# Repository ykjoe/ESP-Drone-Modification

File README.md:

# ESP-Drone

<br>

<br>

For a full tutorial check out our [ESP32 Drone Article](https://circuitdigest.com/microcontroller-projects/DIY-wifi-controlled-drone).
For working video:  [How to build an ESP32 Drone](https://youtu.be/uzZjk0TQKtU).

Drones have rapidly evolved from niche hobbies to versatile tools with a wide range of applications, from photography to agriculture or even for defense and military purposes. Depending on the application, features and payload capacity their price will vary from pocket changes to a few million. Even though the basic principle behind these drones may appear simple, there is a lot of technology and computation that goes behind it for proper operations and a desired result from these drones. For example, maintaining stability while in the air requires precision sensors such as a Gyroscope and proper processing of reading taken with it. In this project we are going to make such a drone which can be easily controlled using our phones.
This DIY drone is small in size and can be built using easily available components such as ESP32 modules, MPU6050 IMU, coreless motors and plastic propellers.

<br>**For anyone who is trying to flash the firmware using ESP32 Flash Download Tool, here are the file offsets for each binary**
<br>**0x1000 bootloader.bin**
<br>**0x8000 partition-table.bin**
<br>**0x10000 ESPDrone.bin**
<br>
[Note: As this projects are very simple we are only providing the code, schemaitic, and a few essential images if you want to get the images or code explanations do check out the Circuit Digest website.
<br>
<br>

Copy from: https://github.com/Circuit-Digest/ESP-Drone.git

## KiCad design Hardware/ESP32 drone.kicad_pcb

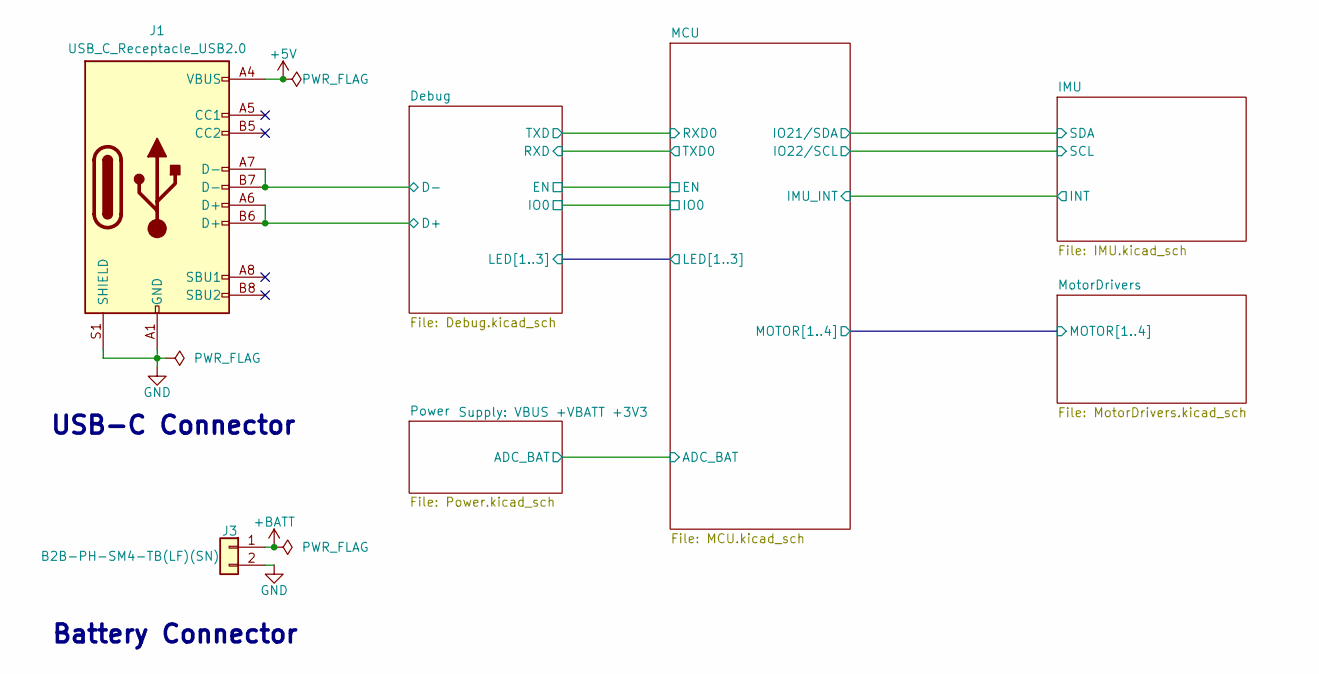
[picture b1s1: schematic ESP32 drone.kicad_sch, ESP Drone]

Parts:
J1: USB_C_Receptacle_USB2.0; USB_C_Receptacle_HRO_TYPE-C-31-M-12
J3: B2B-PH-SM4-TB(LF)(SN); JST_PH_B2B-PH-SM4-TB_1x02-1MP_P2.00mm_Vertical

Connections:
+5V: J1.A4 (VBUS), J1.A9 (VBUS), J1.B4 (VBUS), J1.B9 (VBUS); also elsewhere on the board
+BATT: J3.1; also elsewhere on the board
/Debug/D+: J1.A6 (D+), J1.B6 (D+); also elsewhere on the board
/Debug/D-: J1.A7 (D-), J1.B7 (D-); also elsewhere on the board
GND: J1.A1 (GND), J1.A12 (GND), J1.B1 (GND), J1.B12 (GND), J1.S1 (SHIELD), J3.2; also elsewhere on the board

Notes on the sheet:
Battery Connector
USB-C Connector

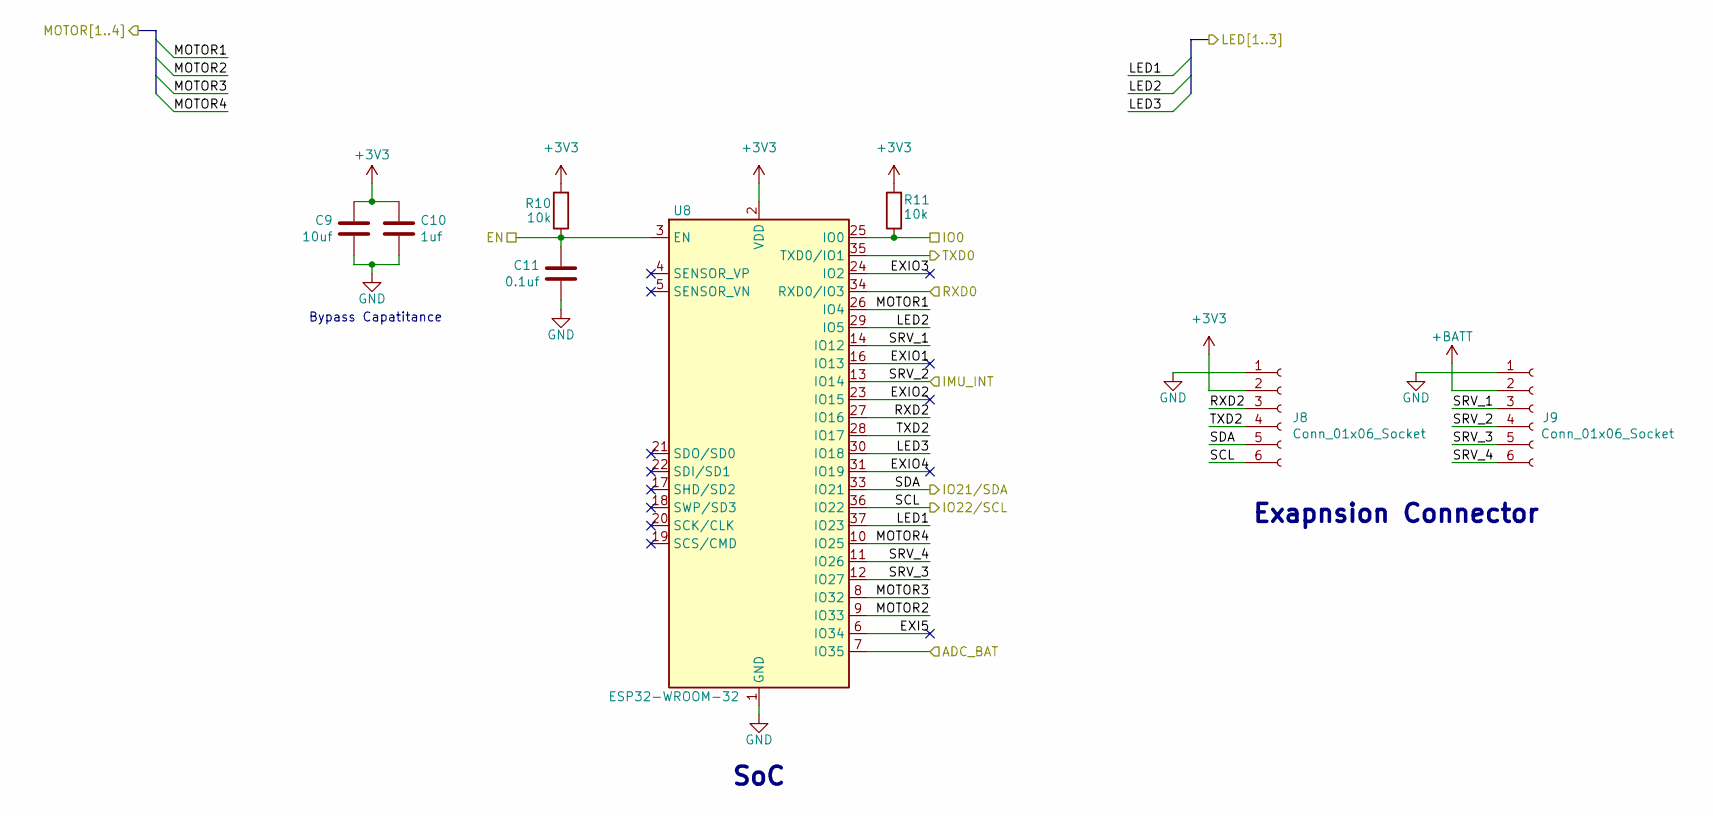
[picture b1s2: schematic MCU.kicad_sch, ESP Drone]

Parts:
C9: 10uf; C_0603_1608Metric
C10: 1uf; C_0603_1608Metric
C11: 0.1uf; C_0603_1608Metric
J8, J9: Conn_01x06_Socket; PinHeader_1x06_P2.54mm_Vertical
R10, R11: 10k; R_0603_1608Metric
U8: ESP32-WROOM-32

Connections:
+3V3: C9.1, C10.1, J8.2, R10.2, R11.2, U8.2 (VDD); also elsewhere on the board
+BATT: J9.2; also elsewhere on the board
/Debug/EN: C11.1, R10.1, U8.3 (EN); also elsewhere on the board
/Debug/IO0: R11.1, U8.25 (IO0); also elsewhere on the board
/Debug/LED1: U8.37 (IO23); also elsewhere on the board
/Debug/LED2: U8.29 (IO5); also elsewhere on the board
/Debug/LED3: U8.30 (IO18); also elsewhere on the board
/Debug/RXD: U8.35 (TXD0/IO1); also elsewhere on the board
/Debug/TXD: U8.34 (RXD0/IO3); also elsewhere on the board
/MCU/ADC_BAT: U8.7 (IO35); also elsewhere on the board
/MCU/EXI5: U8.6 (IO34)
/MCU/EXIO1: U8.16 (IO13)
/MCU/EXIO2: U8.23 (IO15)
/MCU/EXIO3: U8.24 (IO2)
/MCU/EXIO4: U8.31 (IO19)
/MCU/MOTOR1: U8.26 (IO4); also elsewhere on the board
/MCU/MOTOR2: U8.9 (IO33); also elsewhere on the board
/MCU/MOTOR3: U8.8 (IO32); also elsewhere on the board
/MCU/MOTOR4: U8.10 (IO25); also elsewhere on the board
/MCU/RXD2: J8.3, U8.27 (IO16)
/MCU/SCL: J8.6, U8.36 (IO22); also elsewhere on the board
/MCU/SDA: J8.5, U8.33 (IO21); also elsewhere on the board
/MCU/SRV_1: J9.3, U8.14 (IO12)
/MCU/SRV_2: J9.4, U8.13 (IO14); also elsewhere on the board
/MCU/SRV_3: J9.5, U8.12 (IO27)
/MCU/SRV_4: J9.6, U8.11 (IO26)
/MCU/TXD2: J8.4, U8.28 (IO17)
GND: C9.2, C10.2, C11.2, J8.1, J9.1, U8.1 (GND), U8.15 (GND), U8.38 (GND), U8.39 (GND); also elsewhere on the board

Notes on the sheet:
Exapnsion Connector
Bypass Capatitance
SoC

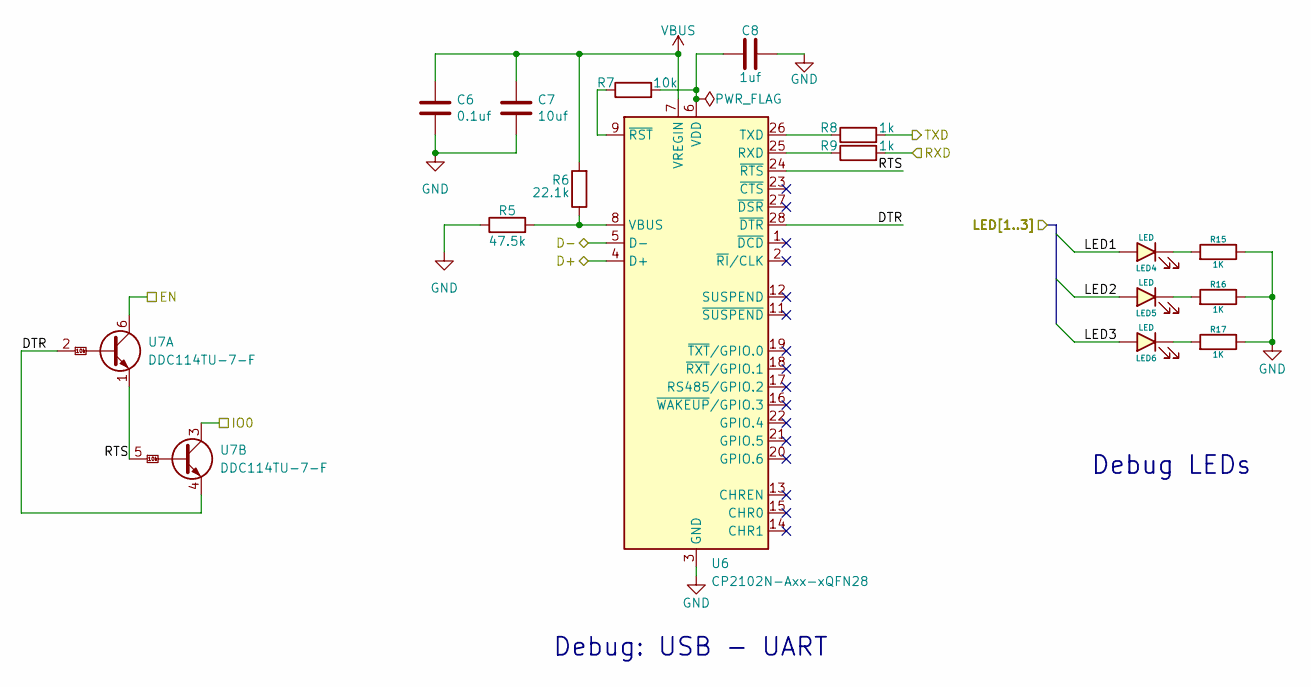
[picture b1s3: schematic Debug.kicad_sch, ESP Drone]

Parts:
C6: 0.1uf; C_0603_1608Metric
C7: 10uf; C_0603_1608Metric
C8: 1uf; C_0603_1608Metric
LED4, LED5, LED6: LED; LED_0603_1608Metric
R5: 47.5k; R_0603_1608Metric
R6: 22.1k; R_0603_1608Metric
R7: 10k; R_0603_1608Metric
R8, R9: 1k; R_0603_1608Metric
R15, R16, R17: 1K; R_0603_1608Metric
U6: CP2102N-Axx-xQFN28; QFN-28-1EP_5x5mm_P0.5mm_EP3.35x3.35mm
U7: DDC114TU-7-F; SOT-363_SC-70-6

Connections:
/Debug/D+: U6.4 (D+); also elsewhere on the board
/Debug/D-: U6.5 (D-); also elsewhere on the board
/Debug/DTR: U6.28 (~DTR), U7.2 (B1), U7.4 (E2)
/Debug/EN: U7.6 (C1); also elsewhere on the board
/Debug/IO0: U7.3 (C2); also elsewhere on the board
/Debug/LED1: LED4.2 (A); also elsewhere on the board
/Debug/LED2: LED5.2 (A); also elsewhere on the board
/Debug/LED3: LED6.2 (A); also elsewhere on the board
/Debug/RTS: U6.24 (~RTS), U7.1 (E1), U7.5 (B2)
/Debug/RXD: R9.2; also elsewhere on the board
/Debug/TXD: R8.2; also elsewhere on the board
GND: C6.2, C7.2, C8.2, R5.1, R15.1, R16.1, R17.1, U6.3 (GND), U6.29 (GND); also elsewhere on the board
unnamed: LED4.1 (K), R15.2
unnamed: LED5.1 (K), R16.2
unnamed: LED6.1 (K), R17.2
unnamed: R9.1, U6.25 (RXD)
unnamed: R8.1, U6.26 (TXD)
unnamed: R5.2, R6.1, U6.8 (VBUS)
unnamed: C8.1, R7.2, U6.6 (VDD)
unnamed: R7.1, U6.9 (~RST)
VBUS: C6.1, C7.1, R6.2, U6.7 (VREGIN); also elsewhere on the board

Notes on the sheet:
Debug LEDs
Debug: USB - UART

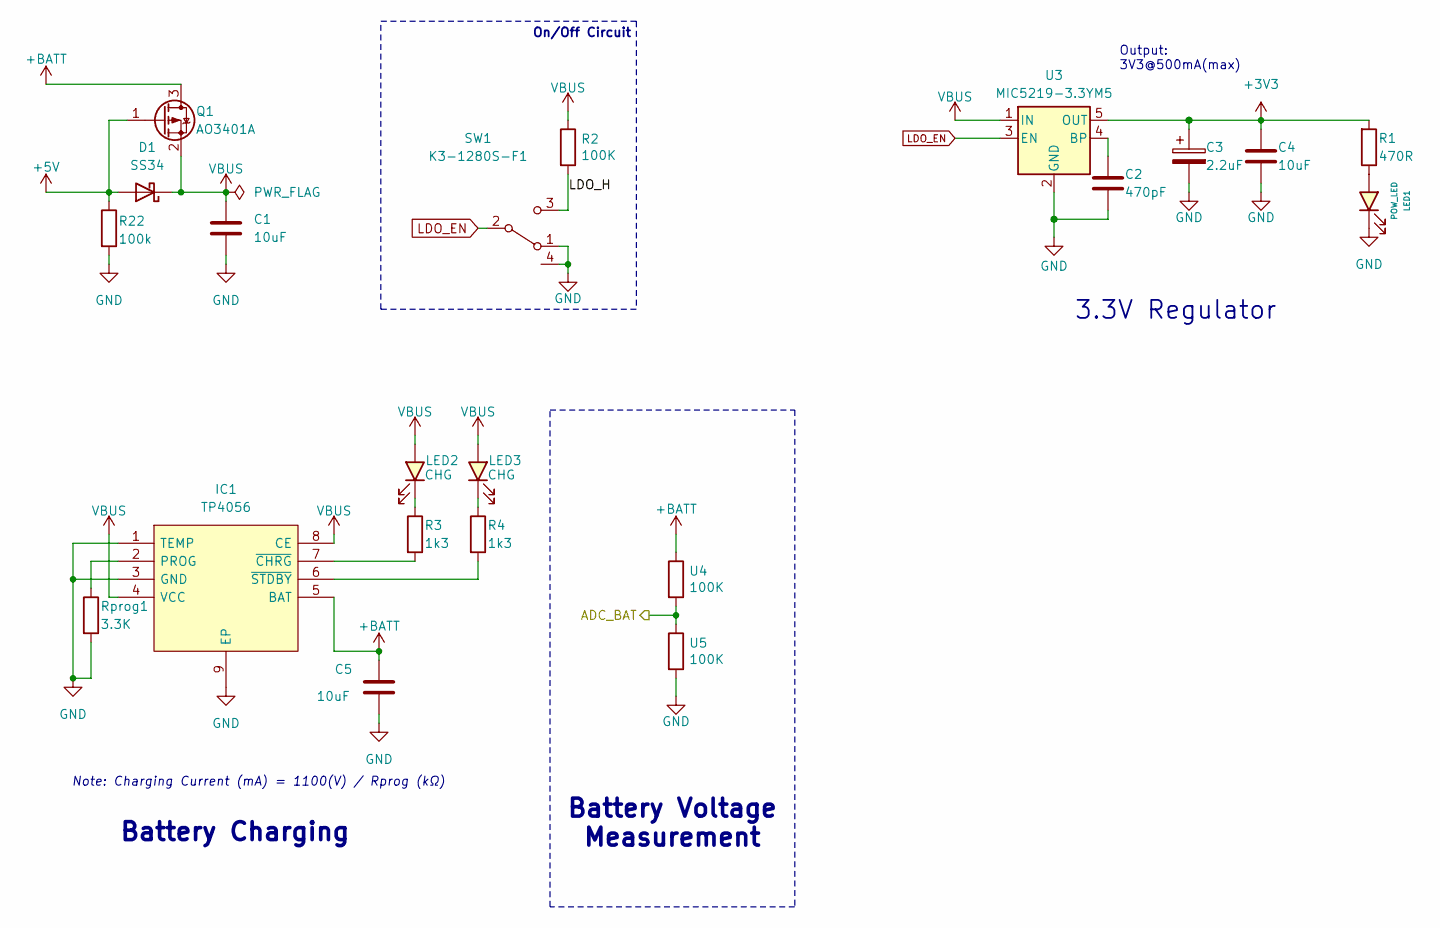
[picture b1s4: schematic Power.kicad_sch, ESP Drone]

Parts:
C1, C4, C5: 10uF; C_0603_1608Metric
C2: 470pF; C_0603_1608Metric
C3: 2.2uF; C_0805_2012Metric
D1: SS34; D_SMA
IC1: TP4056; SOIC127P600X175-9N; Manufacturer_Part_Number TP4056-42-ESOP8
LED1: POW_LED; LED_0603_1608Metric
LED2, LED3: CHG; LED_0603_1608Metric
Q1: AO3401A; SOT-23
R1: 470R; R_0603_1608Metric
R2: 100K; R_0603_1608Metric
R3, R4: 1k3; R_0603_1608Metric
R22: 100k; R_0603_1608Metric
Rprog1: 3.3K; R_0603_1608Metric
SW1: K3-1280S-F1; slide switch spdt
U3: MIC5219-3.3YM5; SOT-23-5
U4, U5: 100K; R_0603_1608Metric

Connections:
+3V3: C3.1, C4.1, R1.2, U3.5 (OUT); also elsewhere on the board
+5V: D1.2 (A), Q1.1 (G), R22.1; also elsewhere on the board
+BATT: C5.1, IC1.5 (BAT), Q1.3 (D), U4.1; also elsewhere on the board
/MCU/ADC_BAT: U4.2, U5.1; also elsewhere on the board
/Power/LDO_H: R2.2, SW1.3 (C)
GND: C1.2, C2.2, C3.2, C4.2, C5.2, IC1.1 (TEMP), IC1.3 (GND), IC1.9 (EP), LED1.1 (K), R22.2, Rprog1.2, SW1.1 (A), SW1.4, U3.2 (GND), U5.2; also elsewhere on the board
LDO_EN: SW1.2 (B), U3.3 (EN)
unnamed: IC1.2 (PROG), Rprog1.1
unnamed: IC1.7 (~CHRG), R3.2
unnamed: IC1.6 (~STDBY), R4.2
unnamed: LED1.2 (A), R1.1
unnamed: LED2.1 (K), R3.1
unnamed: LED3.1 (K), R4.1
unnamed: C2.1, U3.4 (BP)
VBUS: C1.1, D1.1 (K), IC1.4 (VCC), IC1.8 (CE), LED2.2 (A), LED3.2 (A), Q1.2 (S), R2.1, U3.1 (IN); also elsewhere on the board

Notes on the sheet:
Output: 3V3@500mA(max)
Note: Charging Current (mA) = 1100(V) / Rprog (kΩ)
Battery Voltage Measurement
Battery Charging
On/Off Circuit
3.3V Regulator

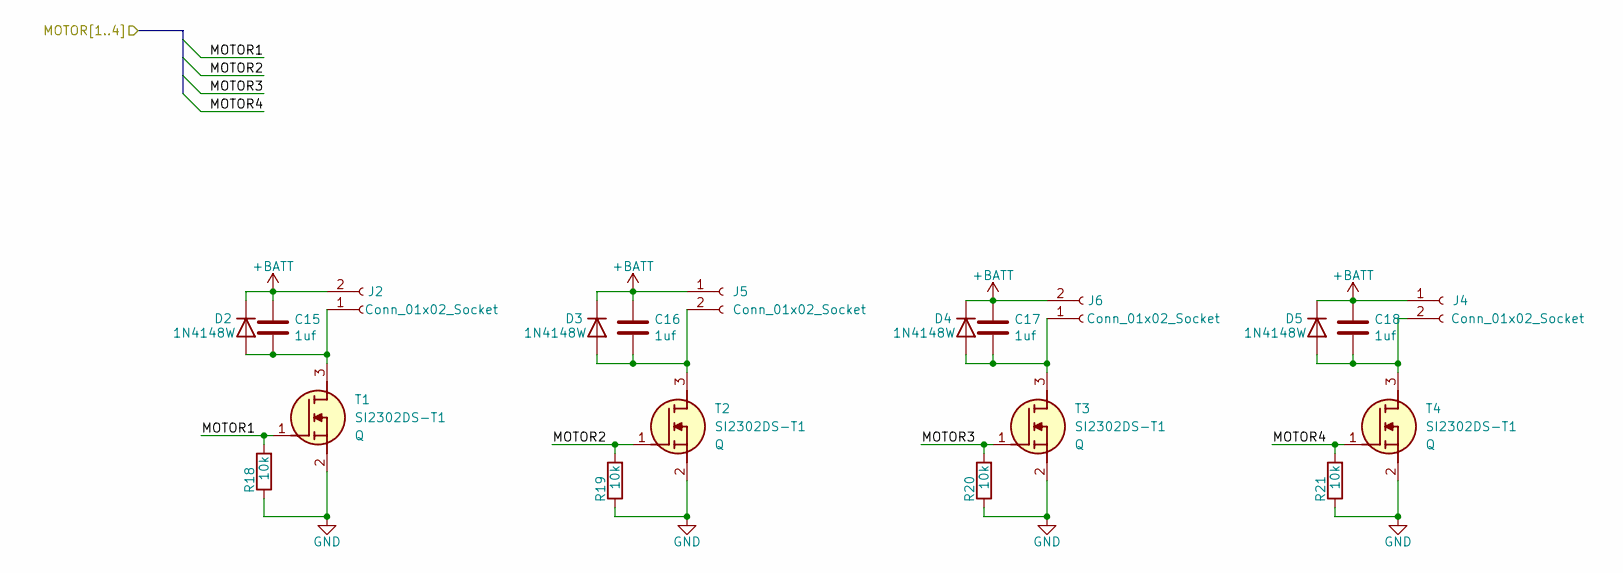
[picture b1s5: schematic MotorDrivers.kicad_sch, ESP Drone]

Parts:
C15, C16, C17, C18: 1uf; C_0603_1608Metric
D2, D3, D4, D5: 1N4148W; D_SOD-123
J2, J4, J5, J6: Conn_01x02_Socket; JST_GH_SM02B-GHS-TB_1x02-1MP_P1.25mm_Horizontal
R18, R19, R20, R21: 10k; R_0603_1608Metric
T1, T2, T3, T4: SI2302DS-T1; SOT95P237X112-3N; Mouser Part Number 781-SI2302DS

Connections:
+BATT: C15.1, C16.1, C17.1, C18.1, D2.1 (K), D3.1 (K), D4.1 (K), D5.1 (K), J2.2, J4.1, J5.1, J6.2; also elsewhere on the board
/MCU/MOTOR1: R18.2, T1.1 (G); also elsewhere on the board
/MCU/MOTOR2: R19.2, T2.1 (G); also elsewhere on the board
/MCU/MOTOR3: R20.2, T3.1 (G); also elsewhere on the board
/MCU/MOTOR4: R21.2, T4.1 (G); also elsewhere on the board
GND: R18.1, R19.1, R20.1, R21.1, T1.2 (S), T2.2 (S), T3.2 (S), T4.2 (S); also elsewhere on the board
unnamed: C15.2, D2.2 (A), J2.1, T1.3 (D)
unnamed: C16.2, D3.2 (A), J5.2, T2.3 (D)
unnamed: C17.2, D4.2 (A), J6.1, T3.3 (D)
unnamed: C18.2, D5.2 (A), J4.2, T4.3 (D)

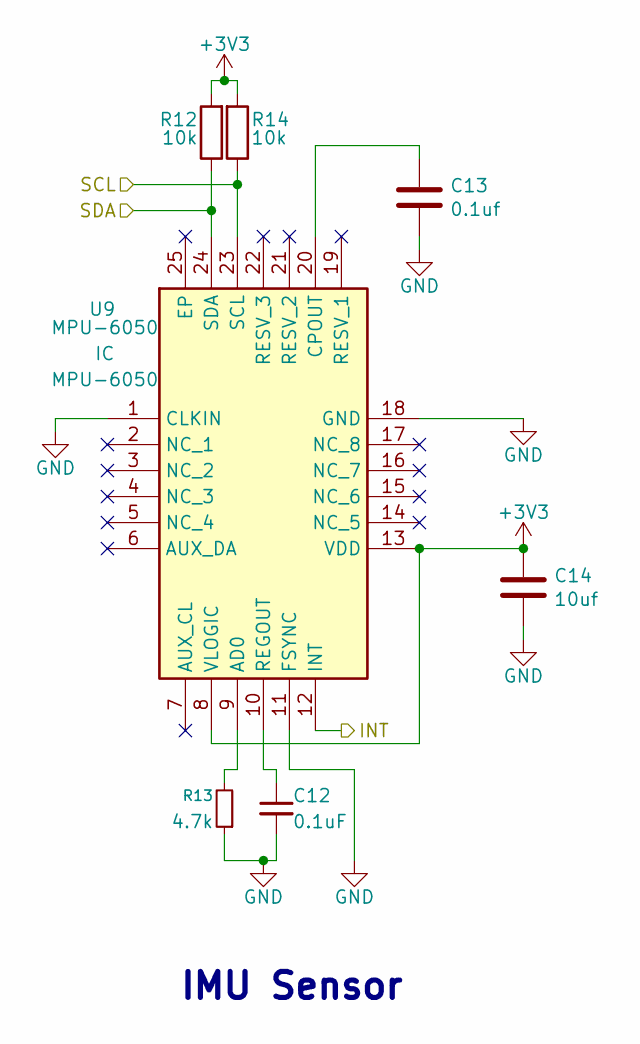
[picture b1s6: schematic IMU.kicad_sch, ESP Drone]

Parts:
C12: 0.1uF; C_0603_1608Metric
C13: 0.1uf; C_0603_1608Metric
C14: 10uf; C_0603_1608Metric
R12, R14: 10k; R_0603_1608Metric
R13: 4.7k; R_0603_1608Metric
U9: MPU-6050; MPU6050; Mouser Part Number 410-MPU-6050

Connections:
+3V3: C14.1, R12.2, R14.2, U9.8 (VLOGIC), U9.13 (VDD); also elsewhere on the board
/MCU/SCL: R14.1, U9.23 (SCL); also elsewhere on the board
/MCU/SDA: R12.1, U9.24 (SDA); also elsewhere on the board
/MCU/SRV_2: U9.12 (INT); also elsewhere on the board
GND: C12.2, C13.2, C14.2, R13.1, U9.1 (CLKIN), U9.11 (FSYNC), U9.18 (GND); also elsewhere on the board
unnamed: R13.2, U9.9 (AD0)
unnamed: C13.1, U9.20 (CPOUT)
unnamed: C12.1, U9.10 (REGOUT)

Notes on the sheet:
IMU Sensor

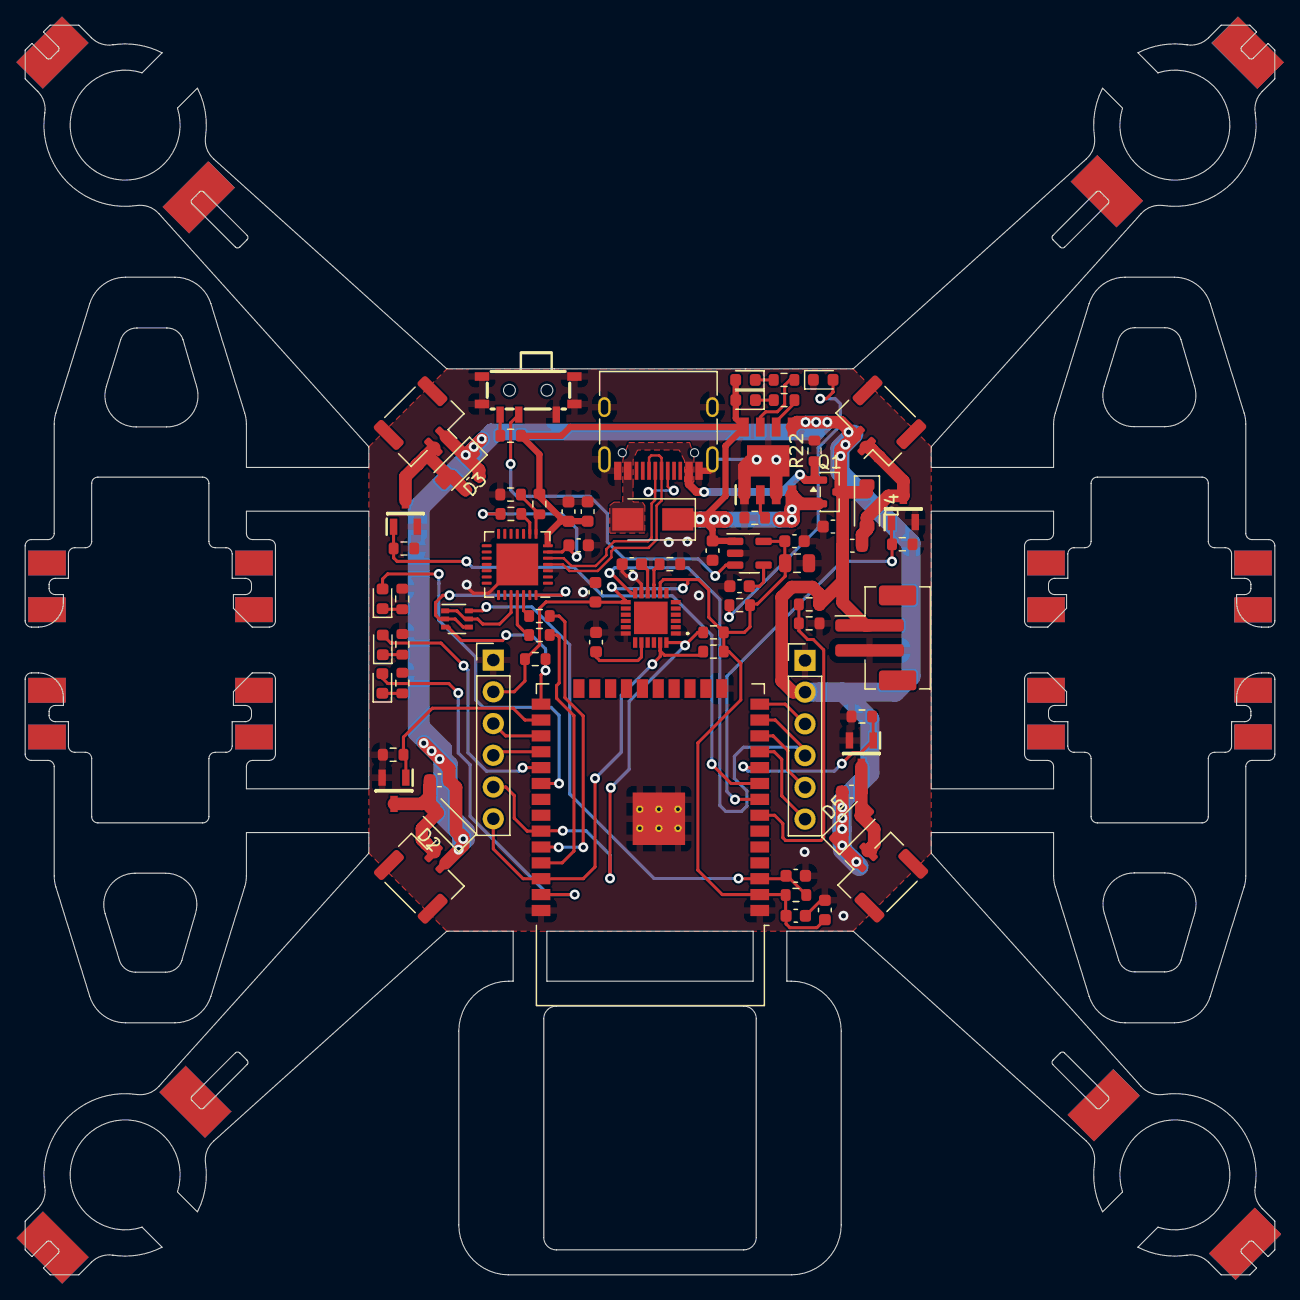
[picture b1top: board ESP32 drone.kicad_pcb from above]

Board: 2 copper layers, 100.0 x 100.0 mm, 74 parts (0 on the bottom side), 53 nets.

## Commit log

2025-10-20 Create repo from Circuit-Digest/ESP-Drone
2025-10-23 Organize drawings and BOM
